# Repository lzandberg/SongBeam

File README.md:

# SongBeam
Songrecorder using beamforming technology

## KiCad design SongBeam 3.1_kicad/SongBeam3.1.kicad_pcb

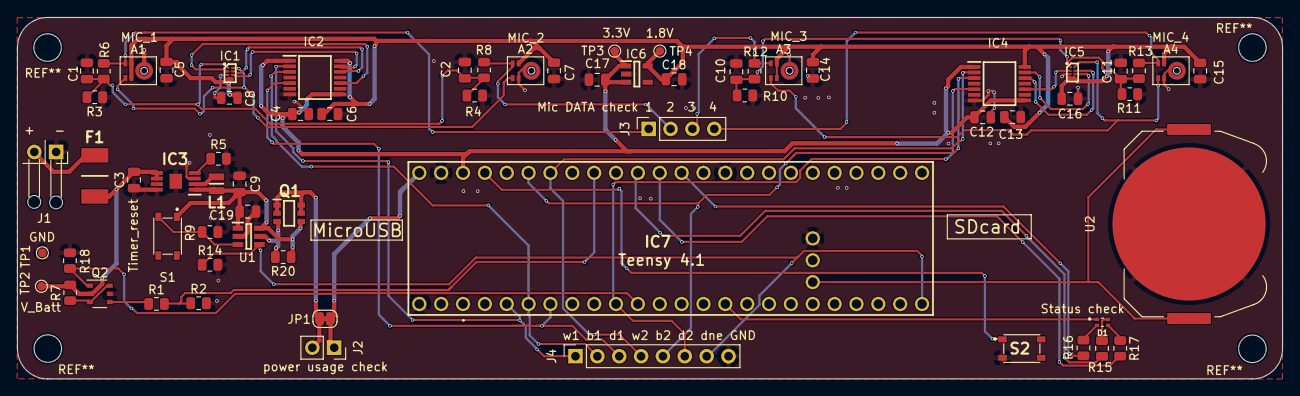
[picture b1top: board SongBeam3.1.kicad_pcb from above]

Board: 2 copper layers, 147.0 x 42.0 mm, 67 parts (0 on the bottom side), 46 nets.

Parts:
A1, A2, A3, A4: IM69D130; Infineon_PG-LLGA-5-1
C1, C2, C10, C11: 47pF; C_0805_2012Metric
C3: 4.7µF; C_0805_2012Metric
C4, C5, C6, C7, C8, C12, C13, C14, C15, C16, C19: 100nF; C_0805_2012Metric
C9: 10µF; C_0805_2012Metric
C17, C18: 1µF; C_0805_2012Metric
D1: APHF1608LSEEQBDZGKC; LED_APHF1608LSEEQBDZGKC
F1: Polyfuse; MINISMDC050F2
IC1, IC5: ADAU7002ACBZ-R7; BGA8C40P2X4_76X156X56
IC2, IC4: TXU0304PWR; SOP65P640X120-14N
IC3: TPS62842DGRR; SOP65P490X110-9N
IC6: LP5907MFX-1.8_NOPB; SOT95P280X145-5N
IC7: TEENSY_4.1; TEENSY41
J1: Conn_01x02; SolderWire_1x02_P2.52
J2: Conn_01x02; PinSocket_1x02_P2.54mm_Vertical
J3: Conn_01x04; PinSocket_1x04_P2.54mm_Vertical
J4: Conn_01x08; PinSocket_1x08_P2.54mm_Vertical
JP1: SolderJumper_2_Bridged; SolderJumper-2_P1.3mm_Bridged_RoundedPad1.0x1.5mm
L1: DFE201612E-2R2M=P2; 1286ASH1R0MP2
Q1: CPH6350-TL-W; SOT95P280X105-6N
Q2: AO6604; TSOP-6_1.65x3.05mm_P0.95mm
R1, R14: 1M; R_0805_2012Metric
R2: 105K; R_0805_2012Metric
R3, R4, R7, R9, R10, R11, R18: 100K; R_0805_2012Metric
R5: 267K; R_0805_2012Metric
R6, R8, R12, R13: 100R; R_0805_2012Metric
R15, R17: 330R; R_0805_2012Metric
R16: 750R; R_0805_2012Metric
R20: NC; R_0805_2012Metric
S1, S2: PTS815_SJM_250_SMTR_LFS; PTS815SJM250SMTRLFS
TP1, TP2, TP3, TP4: TestPoint; TestPoint_Pad_D1.0mm
U1: TPL5110; SOT95P280X110-6N
U2: 3034; BatteryHolder_Keystone_3034_1x20mm

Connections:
+1V8: A1.2 (VDD), A1.4 (SELECT), A2.2 (VDD), A3.2 (VDD), A3.4 (SELECT), A4.2 (VDD), C5.2, C6.1, C7.2, C8.2, C13.1, C14.2, C15.2, C16.2, C18.1, IC1.D1 (IOVDD), IC1.D2 (CONFIG), IC2.14 (VCCB), IC4.14 (VCCB), IC5.D1 (IOVDD), IC5.D2 (CONFIG), IC6.5 (OUT), TP4.1
+3.3V: C4.1, C12.1, C17.2, IC2.1 (VCCA), IC2.8 (OE), IC4.1 (VCCA), IC4.8 (OE), IC6.1 (IN), IC6.3 (EN), IC7.53 (3.3V_(250_M_A_MAX)), TP3.1
GND: A1.5 (GND), A2.4 (SELECT), A2.5 (GND), A3.5 (GND), A4.4 (SELECT), A4.5 (GND), C1.2, C2.2, C3.1, C4.2, C5.1, C6.2, C7.1, C8.1, C9.2, C10.2, C11.2, C12.2, C13.2, C14.1, C15.1, C16.1, C17.1, C18.2, C19.2, IC1.C1 (GND), IC2.7 (GND), IC3.3 (MODE), IC3.8 (GND_1), IC3.9 (GND_2), IC4.7 (GND), IC5.C1 (GND), IC6.2 (GND), IC7.45 (GND_1), IC7.69 (GND_4), IC7.70 (GND_5), IC7.71 (GND_6), J1.1, J4.8, Q2.5 (S1), R2.2, R3.2, R4.2, R5.2, R9.2, R10.2, R11.2, R14.2, R18.2, S2.3 (NO_1), TP1.1, U1.2 (GND), U2.3 (NEG._CONTACT_PAD_(GND))
unnamed: A1.1 (DATA), J3.1, R6.1
unnamed: A1.3 (CLOCK), A2.3 (CLOCK), IC1.A2 (PDM_CLK)
unnamed: A2.1 (DATA), J3.2, R8.1
unnamed: A3.1 (DATA), J3.3, R12.1
unnamed: A3.3 (CLOCK), A4.3 (CLOCK), IC5.A2 (PDM_CLK)
unnamed: A4.1 (DATA), J3.4, R13.1
unnamed: C1.1, C2.1, IC1.A1 (PDM_DAT), R3.1, R4.1, R6.2, R8.2
unnamed: C3.2, F1.2, IC3.5 (EN), IC3.6 (VIN), Q2.2 (S2), R7.2, TP2.1
unnamed: C10.1, C11.1, IC5.A1 (PDM_DAT), R10.1, R11.1, R12.2, R13.2
unnamed: C9.1, C19.1, IC3.1 (VOS), L1.2, Q1.4 (SOURCE), R20.1, S1.1 (COM_1), U1.1 (VDD), U1.6 (EN/ONE_SHOT)
unnamed: D1.1, IC7.42 (3.3V_1)
unnamed: D1.2, R16.1
unnamed: D1.3, R17.1
unnamed: D1.4, R15.1
unnamed: F1.1, J1.2
unnamed: IC1.B1 (SDATA), IC2.10 (B4)
unnamed: IC1.B2 (BCLK), IC2.12 (B2Y)
unnamed: IC1.C2 (LRCLK), IC2.13 (B1Y)
unnamed: IC2.2 (A1), IC7.3 (LRCLK2), J4.1
unnamed: IC2.3 (A2), IC7.4 (BCLK2), J4.2
unnamed: IC2.5 (A4Y), IC7.5 (IN2), J4.3
unnamed: IC3.2 (SW), L1.1
unnamed: IC3.4 (VSET), R5.1
unnamed: IC4.2 (A1), IC7.20 (A6), J4.4
unnamed: IC4.3 (A2), IC7.21 (A7), J4.5
unnamed: IC4.5 (A4Y), IC7.8 (TX2), J4.6
unnamed: IC4.10 (B4), IC5.B1 (SDATA)
unnamed: IC4.12 (B2Y), IC5.B2 (BCLK)
unnamed: IC4.13 (B1Y), IC5.C2 (LRCLK)
unnamed: IC7.9 (OUT1C), Q2.1 (G1), R18.1
unnamed: IC7.14 (A0), R16.2
unnamed: IC7.15 (A1), R17.2
unnamed: IC7.16 (A2), R15.2
unnamed: IC7.18 (A4), R1.2, R2.1
unnamed: IC7.23 (A9), S2.1 (COM_1)
unnamed: IC7.32 (OUT1B), J4.7, R14.1, U1.4 (DONE)
unnamed: IC7.43 (VBAT), U2.1, U2.2
unnamed: IC7.55 (VIN_(3.6_TO_5.5_VOLTS)), J2.1, JP1.2 (B)
unnamed: J2.2, JP1.1 (A), Q1.1 (DRAIN_1), Q1.2 (DRAIN_2), Q1.5 (DRAIN_3), Q1.6 (DRAIN_4)
unnamed: Q1.3 (GATE), R20.2, U1.5 (DRV)
unnamed: Q2.3 (G2), Q2.6 (D1), R7.1
unnamed: Q2.4 (D2), R1.1
unnamed: R9.1, S1.3 (NO_1), U1.3 (DELAY/M_DRV)

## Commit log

2022-12-05 Initial commit
    Added files
2022-12-05 Create LICENSE.md
    Added Creative Commons Attribution 4.0 International License
2022-12-05 Added recording code
2022-12-05 Create test
2022-12-05 Rename SongBeam4C/SongBeam4C.ino to SongBeam4C/code/SongBeam4C.ino
2022-12-05 Rename SongBeam4C/code/SongBeam4C.ino to SongBeam4C/SongBeam4C.ino
2022-12-05 Rename SongBeam4C/SongBeam4C.ino to SongBeam4C.ino
2022-12-05 Rename SongBeam4C.ino to code/SongBeam4C.ino
2022-12-05 Add hardware files
2023-12-08 Add Enclosure files
2023-12-08 Added photos

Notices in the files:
SongBeam 3.1_kicad/SongBeam3.1.kicad_pcb:
CC BY 4.0
